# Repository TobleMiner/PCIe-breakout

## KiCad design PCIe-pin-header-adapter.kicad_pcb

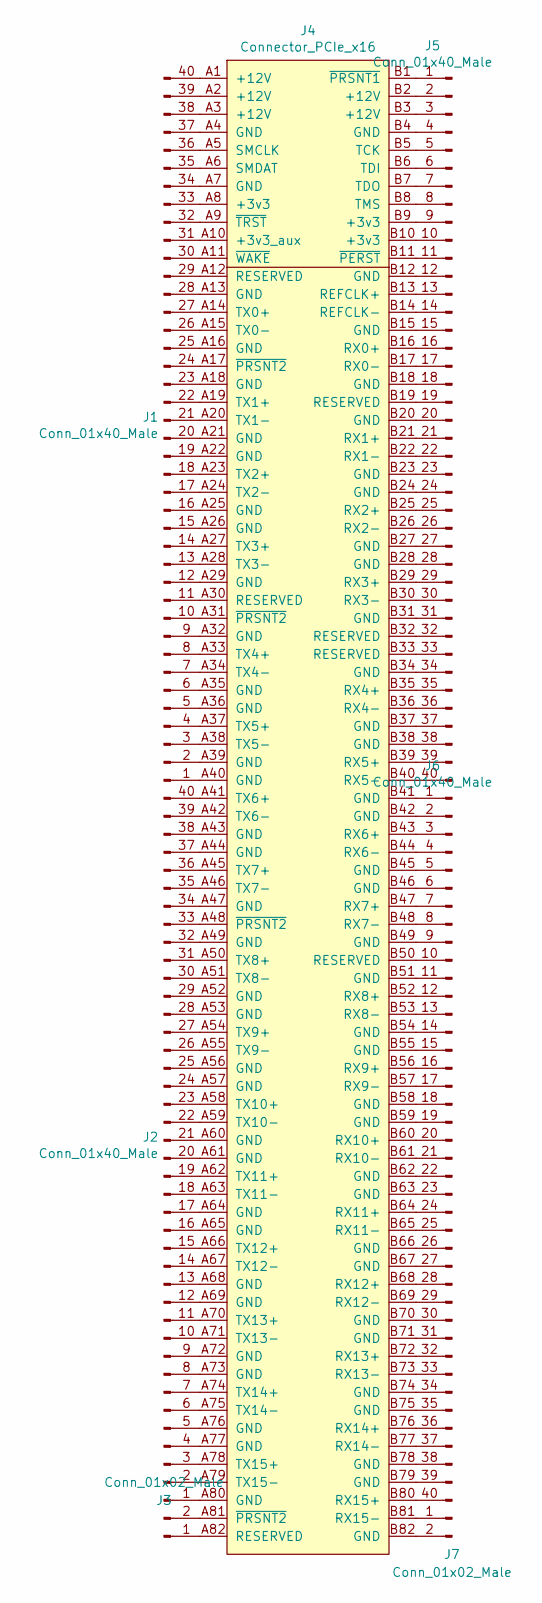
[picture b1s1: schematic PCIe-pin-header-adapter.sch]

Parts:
J1, J2, J5, J6: Conn_01x40_Male; Connector_PinHeader_EdgeLaunch_2,54mm_01x40
J3, J7: Conn_01x02_Male; Connector_PinHeader_EdgeLaunch_2,54mm_01x02
J4: Connector_PCIe_x16; UMAX_3126-10103T_PCIe_x16_edge_launch

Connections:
unnamed: J1.1, J4.A40 (GND)
unnamed: J1.2, J4.A39 (GND)
unnamed: J1.3, J4.A38 (TX5-)
unnamed: J1.4, J4.A37 (TX5+)
unnamed: J1.5, J4.A36 (GND)
unnamed: J1.6, J4.A35 (GND)
unnamed: J1.7, J4.A34 (TX4-)
unnamed: J1.8, J4.A33 (TX4+)
unnamed: J1.9, J4.A32 (GND)
unnamed: J1.10, J4.A31 (~PRSNT2)
unnamed: J1.11, J4.A30 (RESERVED)
unnamed: J1.12, J4.A29 (GND)
unnamed: J1.13, J4.A28 (TX3-)
unnamed: J1.14, J4.A27 (TX3+)
unnamed: J1.15, J4.A26 (GND)
unnamed: J1.16, J4.A25 (GND)
unnamed: J1.17, J4.A24 (TX2-)
unnamed: J1.18, J4.A23 (TX2+)
unnamed: J1.19, J4.A22 (GND)
unnamed: J1.20, J4.A21 (GND)
unnamed: J1.21, J4.A20 (TX1-)
unnamed: J1.22, J4.A19 (TX1+)
unnamed: J1.23, J4.A18 (GND)
unnamed: J1.24, J4.A17 (~PRSNT2)
unnamed: J1.25, J4.A16 (GND)
unnamed: J1.26, J4.A15 (TX0-)
unnamed: J1.27, J4.A14 (TX0+)
unnamed: J1.28, J4.A13 (GND)
unnamed: J1.29, J4.A12 (RESERVED)
unnamed: J1.30, J4.A11 (~WAKE)
unnamed: J1.31, J4.A10 (+3v3_aux)
unnamed: J1.32, J4.A9 (~TRST)
unnamed: J1.33, J4.A8 (+3v3)
unnamed: J1.34, J4.A7 (GND)
unnamed: J1.35, J4.A6 (SMDAT)
unnamed: J1.36, J4.A5 (SMCLK)
unnamed: J1.37, J4.A4 (GND)
unnamed: J1.38, J4.A3 (+12V)
unnamed: J1.39, J4.A2 (+12V)
unnamed: J1.40, J4.A1 (+12V)
unnamed: J2.1, J4.A80 (GND)
unnamed: J2.2, J4.A79 (TX15-)
unnamed: J2.3, J4.A78 (TX15+)
unnamed: J2.4, J4.A77 (GND)
unnamed: J2.5, J4.A76 (GND)
unnamed: J2.6, J4.A75 (TX14-)
unnamed: J2.7, J4.A74 (TX14+)
unnamed: J2.8, J4.A73 (GND)
unnamed: J2.9, J4.A72 (GND)
unnamed: J2.10, J4.A71 (TX13-)
unnamed: J2.11, J4.A70 (TX13+)
unnamed: J2.12, J4.A69 (GND)
unnamed: J2.13, J4.A68 (GND)
unnamed: J2.14, J4.A67 (TX12-)
unnamed: J2.15, J4.A66 (TX12+)
unnamed: J2.16, J4.A65 (GND)
unnamed: J2.17, J4.A64 (GND)
unnamed: J2.18, J4.A63 (TX11-)
unnamed: J2.19, J4.A62 (TX11+)
unnamed: J2.20, J4.A61 (GND)
unnamed: J2.21, J4.A60 (GND)
unnamed: J2.22, J4.A59 (TX10-)
unnamed: J2.23, J4.A58 (TX10+)
unnamed: J2.24, J4.A57 (GND)
unnamed: J2.25, J4.A56 (GND)
unnamed: J2.26, J4.A55 (TX9-)
unnamed: J2.27, J4.A54 (TX9+)
unnamed: J2.28, J4.A53 (GND)
unnamed: J2.29, J4.A52 (GND)
unnamed: J2.30, J4.A51 (TX8-)
unnamed: J2.31, J4.A50 (TX8+)
unnamed: J2.32, J4.A49 (GND)
unnamed: J2.33, J4.A48 (~PRSNT2)
unnamed: J2.34, J4.A47 (GND)
unnamed: J2.35, J4.A46 (TX7-)
unnamed: J2.36, J4.A45 (TX7+)
unnamed: J2.37, J4.A44 (GND)
unnamed: J2.38, J4.A43 (GND)
unnamed: J2.39, J4.A42 (TX6-)
unnamed: J2.40, J4.A41 (TX6+)
unnamed: J3.1, J4.A82 (RESERVED)
unnamed: J3.2, J4.A81 (~PRSNT2)
unnamed: J4.B1 (~PRSNT1), J5.1
unnamed: J4.B2 (+12V), J5.2
unnamed: J4.B3 (+12V), J5.3
unnamed: J4.B4 (GND), J5.4
unnamed: J4.B5 (TCK), J5.5
unnamed: J4.B6 (TDI), J5.6
unnamed: J4.B7 (TDO), J5.7
unnamed: J4.B8 (TMS), J5.8
unnamed: J4.B9 (+3v3), J5.9
unnamed: J4.B10 (+3v3), J5.10
unnamed: J4.B11 (~PERST), J5.11
unnamed: J4.B12 (GND), J5.12
unnamed: J4.B13 (REFCLK+), J5.13
unnamed: J4.B14 (REFCLK-), J5.14
unnamed: J4.B15 (GND), J5.15
unnamed: J4.B16 (RX0+), J5.16
unnamed: J4.B17 (RX0-), J5.17
unnamed: J4.B18 (GND), J5.18
unnamed: J4.B19 (RESERVED), J5.19
unnamed: J4.B20 (GND), J5.20
unnamed: J4.B21 (RX1+), J5.21
unnamed: J4.B22 (RX1-), J5.22
unnamed: J4.B23 (GND), J5.23
unnamed: J4.B24 (GND), J5.24
unnamed: J4.B25 (RX2+), J5.25
unnamed: J4.B26 (RX2-), J5.26
unnamed: J4.B27 (GND), J5.27
unnamed: J4.B28 (GND), J5.28
unnamed: J4.B29 (RX3+), J5.29
unnamed: J4.B30 (RX3-), J5.30
unnamed: J4.B31 (GND), J5.31
unnamed: J4.B32 (RESERVED), J5.32
unnamed: J4.B33 (RESERVED), J5.33
unnamed: J4.B34 (GND), J5.34
unnamed: J4.B35 (RX4+), J5.35
unnamed: J4.B36 (RX4-), J5.36
unnamed: J4.B37 (GND), J5.37
unnamed: J4.B38 (GND), J5.38
unnamed: J4.B39 (RX5+), J5.39
unnamed: J4.B40 (RX5-), J5.40
unnamed: J4.B41 (GND), J6.1
unnamed: J4.B42 (GND), J6.2
unnamed: J4.B43 (RX6+), J6.3
unnamed: J4.B44 (RX6-), J6.4
unnamed: J4.B45 (GND), J6.5
unnamed: J4.B46 (GND), J6.6
unnamed: J4.B47 (RX7+), J6.7
unnamed: J4.B48 (RX7-), J6.8
unnamed: J4.B49 (GND), J6.9
unnamed: J4.B50 (RESERVED), J6.10
unnamed: J4.B51 (GND), J6.11
unnamed: J4.B52 (RX8+), J6.12
unnamed: J4.B53 (RX8-), J6.13
unnamed: J4.B54 (GND), J6.14
unnamed: J4.B55 (GND), J6.15
unnamed: J4.B56 (RX9+), J6.16
unnamed: J4.B57 (RX9-), J6.17
unnamed: J4.B58 (GND), J6.18
unnamed: J4.B59 (GND), J6.19
unnamed: J4.B60 (RX10+), J6.20
unnamed: J4.B61 (RX10-), J6.21
unnamed: J4.B62 (GND), J6.22
unnamed: J4.B63 (GND), J6.23
unnamed: J4.B64 (RX11+), J6.24
unnamed: J4.B65 (RX11-), J6.25
unnamed: J4.B66 (GND), J6.26
unnamed: J4.B67 (GND), J6.27
unnamed: J4.B68 (RX12+), J6.28
unnamed: J4.B69 (RX12-), J6.29
unnamed: J4.B70 (GND), J6.30
unnamed: J4.B71 (GND), J6.31
unnamed: J4.B72 (RX13+), J6.32
unnamed: J4.B73 (RX13-), J6.33
unnamed: J4.B74 (GND), J6.34
unnamed: J4.B75 (GND), J6.35
unnamed: J4.B76 (RX14+), J6.36
unnamed: J4.B77 (RX14-), J6.37
unnamed: J4.B78 (GND), J6.38
unnamed: J4.B79 (GND), J6.39
unnamed: J4.B80 (RX15+), J6.40
unnamed: J4.B81 (RX15-), J7.1
unnamed: J4.B82 (GND), J7.2

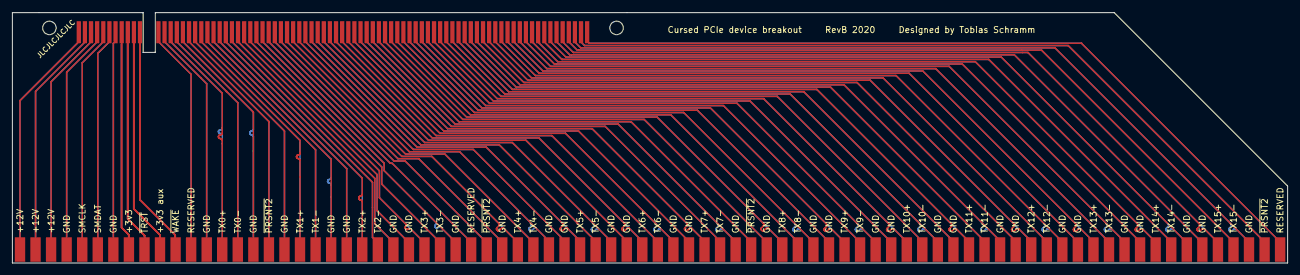
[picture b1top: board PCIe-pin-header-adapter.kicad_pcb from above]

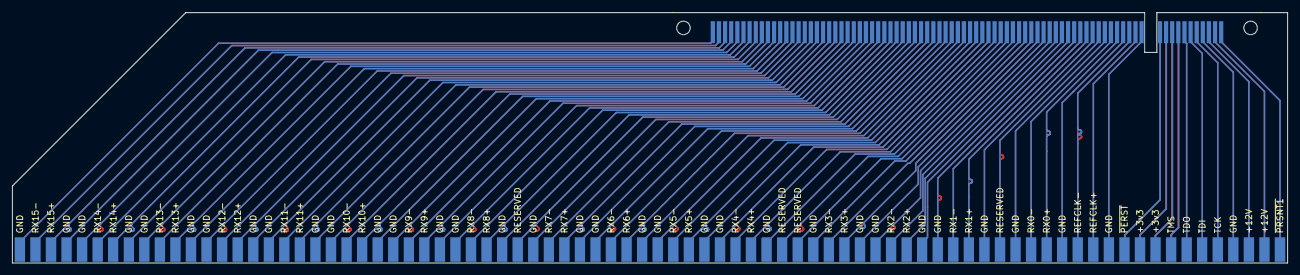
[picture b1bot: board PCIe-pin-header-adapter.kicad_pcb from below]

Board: 2 copper layers, 208.1 x 40.8 mm, 7 parts (3 on the bottom side), 164 nets.

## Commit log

2020-09-14 Deepen PCIe x16 slot cutout
2020-09-14 Add fabrication files
2020-09-14 Add license
